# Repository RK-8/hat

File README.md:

# RK8 - HAT

This repository contains Eagle based source files for constructing Raspberry Pi
HAT allowing to connect a 32x32 LED matrix and 8 switches (4 for a joystick) and
4 regular ones.

## Level 3

## Level 2

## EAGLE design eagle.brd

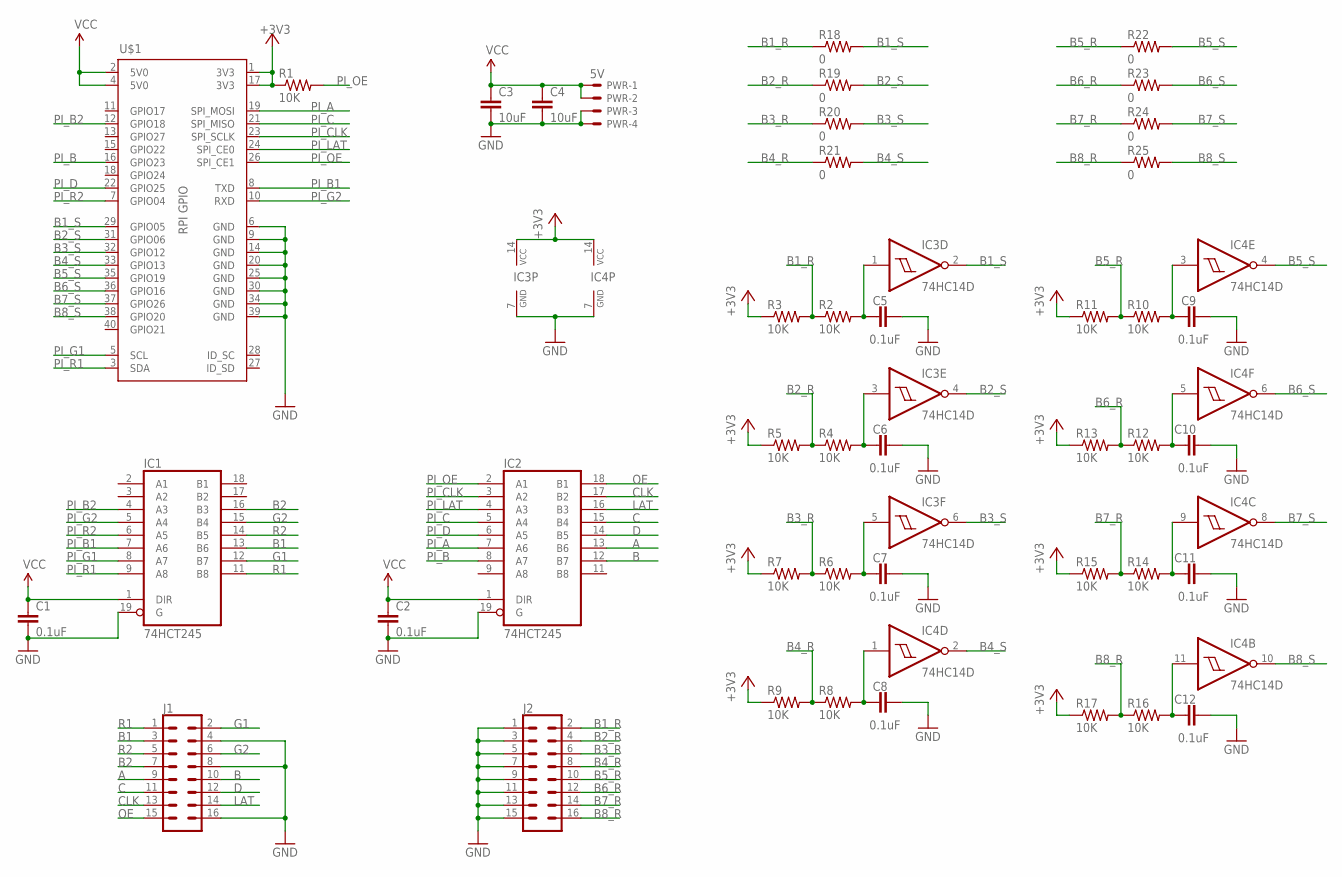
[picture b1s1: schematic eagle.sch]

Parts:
C1, C2, C5, C6, C7, C8, C9, C10, C11, C12: 0.1uF; 0805
C3, C4: 10uF; 0805
IC1, IC2: 74HCT245; SO20W
IC3, IC4: 74HC14D; SO14
J1, J2: CONN_08X2_SHROUD; 2X8-SHROUDED_LOCK
PWR: 5V; KK-156-4
R1, R2, R3, R4, R5, R6, R7, R8, R9, R10, R11, R12, R13, R14, R15, R16, R17: 10K; 0805
R18, R19, R20, R21, R22, R23, R24, R25: 0; 0805
U$1: RPI3_HATNO_DF; RASPI_BOARD_B+HAT

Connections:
+3V3: IC3.14 (VCC), IC4.14 (VCC), R1.1, R3.1, R5.1, R7.1, R9.1, R11.1, R13.1, R15.1, R17.1, U$1.1 (3V3), U$1.17 (3V3)
A: IC2.13 (B6), J1.9
B: IC2.12 (B7), J1.10
B1: IC1.13 (B6), J1.3
B1_R: J2.2, R2.1, R3.2, R18.1
B1_S: IC3.2 (O), R18.2, U$1.29 (GPIO05)
B2: IC1.16 (B3), J1.7
B2_R: J2.4, R4.1, R5.2, R19.1
B2_S: IC3.4 (O), R19.2, U$1.31 (GPIO06)
B3_R: J2.6, R6.1, R7.2, R20.1
B3_S: IC3.6 (O), R20.2, U$1.32 (GPIO12)
B4_R: J2.8, R8.1, R9.2, R21.1
B4_S: IC4.2 (O), R21.2, U$1.33 (GPIO13)
B5_R: J2.10, R10.1, R11.2, R22.1
B5_S: IC4.4 (O), R22.2, U$1.35 (GPIO19)
B6_R: J2.12, R12.1, R13.2, R23.1
B6_S: IC4.6 (O), R23.2, U$1.36 (GPIO16)
B7_R: J2.14, R14.1, R15.2, R24.1
B7_S: IC4.8 (O), R24.2, U$1.37 (GPIO26)
B8_R: J2.16, R16.1, R17.2, R25.1
B8_S: IC4.10 (O), R25.2, U$1.38 (GPIO20)
C: IC2.15 (B4), J1.11
CLK: IC2.17 (B2), J1.13
D: IC2.14 (B5), J1.12
G1: IC1.12 (B7), J1.2
G2: IC1.15 (B4), J1.6
GND: C1.2, C2.2, C3.2, C4.2, C5.2, C6.2, C7.2, C8.2, C9.2, C10.2, C11.2, C12.2, IC1.10 (GND), IC1.19 (G), IC2.10 (GND), IC2.19 (G), IC3.7 (GND), IC4.7 (GND), J1.4, J1.8, J1.16, J2.1, J2.3, J2.5, J2.7, J2.9, J2.11, J2.13, J2.15, PWR.3, PWR.4, U$1.6 (GND), U$1.9 (GND), U$1.14 (GND), U$1.20 (GND), U$1.25 (GND), U$1.30 (GND), U$1.34 (GND), U$1.39 (GND)
LAT: IC2.16 (B3), J1.14
unnamed: C5.1, IC3.1 (I), R2.2
unnamed: C6.1, IC3.3 (I), R4.2
unnamed: C7.1, IC3.5 (I), R6.2
unnamed: C8.1, IC4.1 (I), R8.2
unnamed: C9.1, IC4.3 (I), R10.2
unnamed: C10.1, IC4.5 (I), R12.2
unnamed: C11.1, IC4.9 (I), R14.2
unnamed: C12.1, IC4.11 (I), R16.2
OE: IC2.18 (B1), J1.15
PI_A: IC2.7 (A6), U$1.19 (SPI_MOSI)
PI_B: IC2.8 (A7), U$1.16 (GPIO23)
PI_B1: IC1.7 (A6), U$1.8 (TXD)
PI_B2: IC1.4 (A3), U$1.12 (GPIO18)
PI_C: IC2.5 (A4), U$1.21 (SPI_MISO)
PI_CLK: IC2.3 (A2), U$1.23 (SPI_SCLK)
PI_D: IC2.6 (A5), U$1.22 (GPIO25)
PI_G1: IC1.8 (A7), U$1.5 (SCL)
PI_G2: IC1.5 (A4), U$1.10 (RXD)
PI_LAT: IC2.4 (A3), U$1.24 (SPI_CE0)
PI_OE: IC2.2 (A1), R1.2, U$1.26 (SPI_CE1)
PI_R1: IC1.9 (A8), U$1.3 (SDA)
PI_R2: IC1.6 (A5), U$1.7 (GPIO04)
R1: IC1.11 (B8), J1.1
R2: IC1.14 (B5), J1.5
VCC: C1.1, C2.1, C3.1, C4.1, IC1.1 (DIR), IC1.20 (VCC), IC2.1 (DIR), IC2.20 (VCC), PWR.1, PWR.2, U$1.2 (5V0), U$1.4 (5V0)

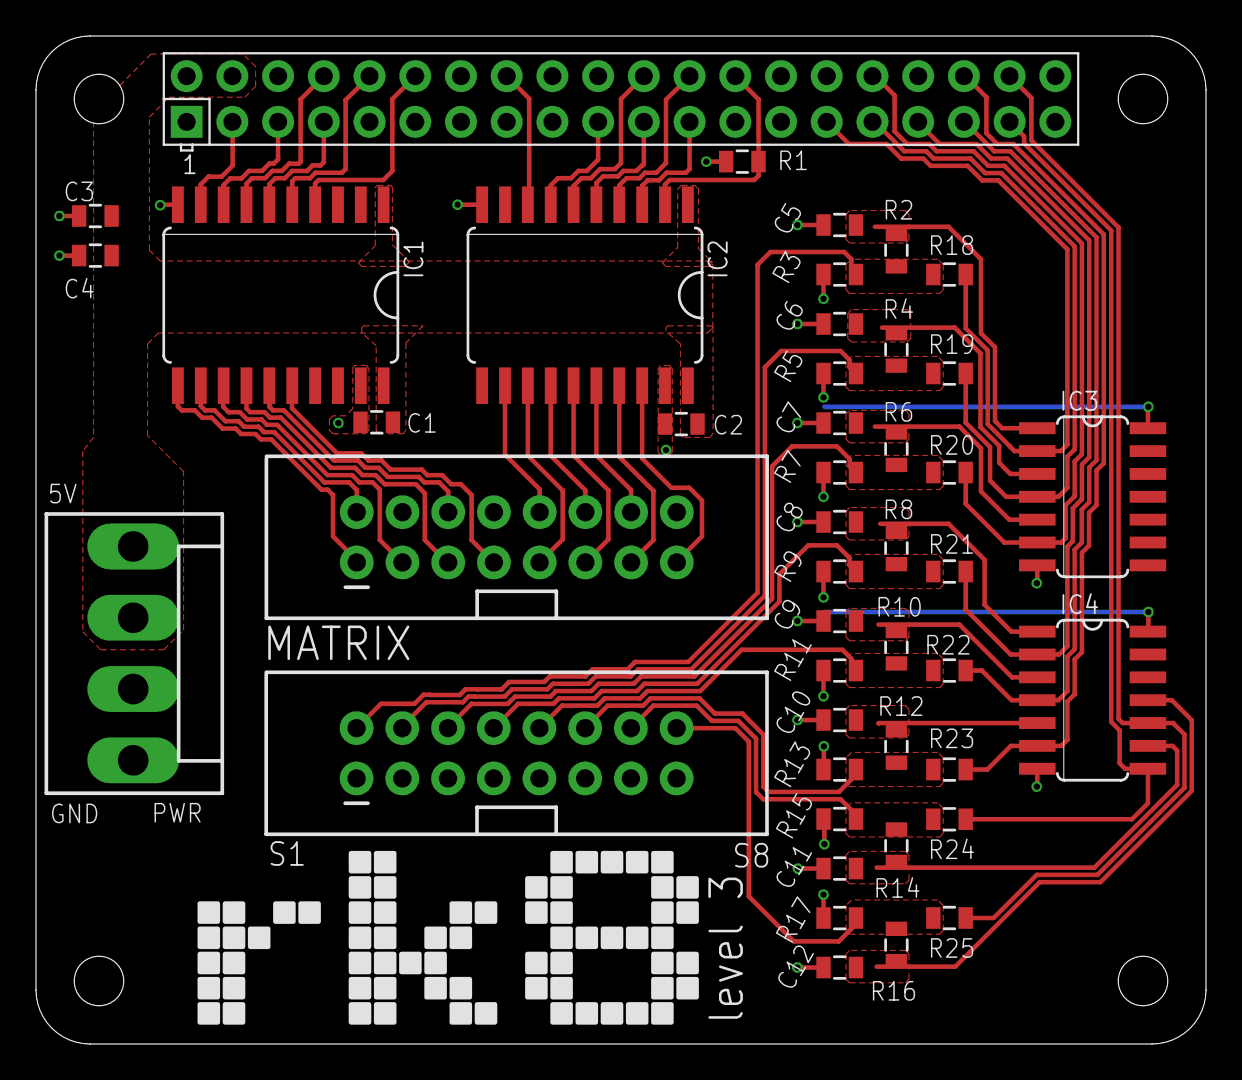
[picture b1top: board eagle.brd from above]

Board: 2 copper layers, 65.0 x 56.0 mm, 45 parts (0 on the bottom side), 53 nets.

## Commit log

2019-08-24 initial commit of the level 2 HAT
2019-08-27 level 3 design

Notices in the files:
parts and their libraries:
SparkFun-Connectors: Licensing: Creative Commons ShareAlike 4.0 International - https://creativecommons.org/licenses/by-sa/4.0
